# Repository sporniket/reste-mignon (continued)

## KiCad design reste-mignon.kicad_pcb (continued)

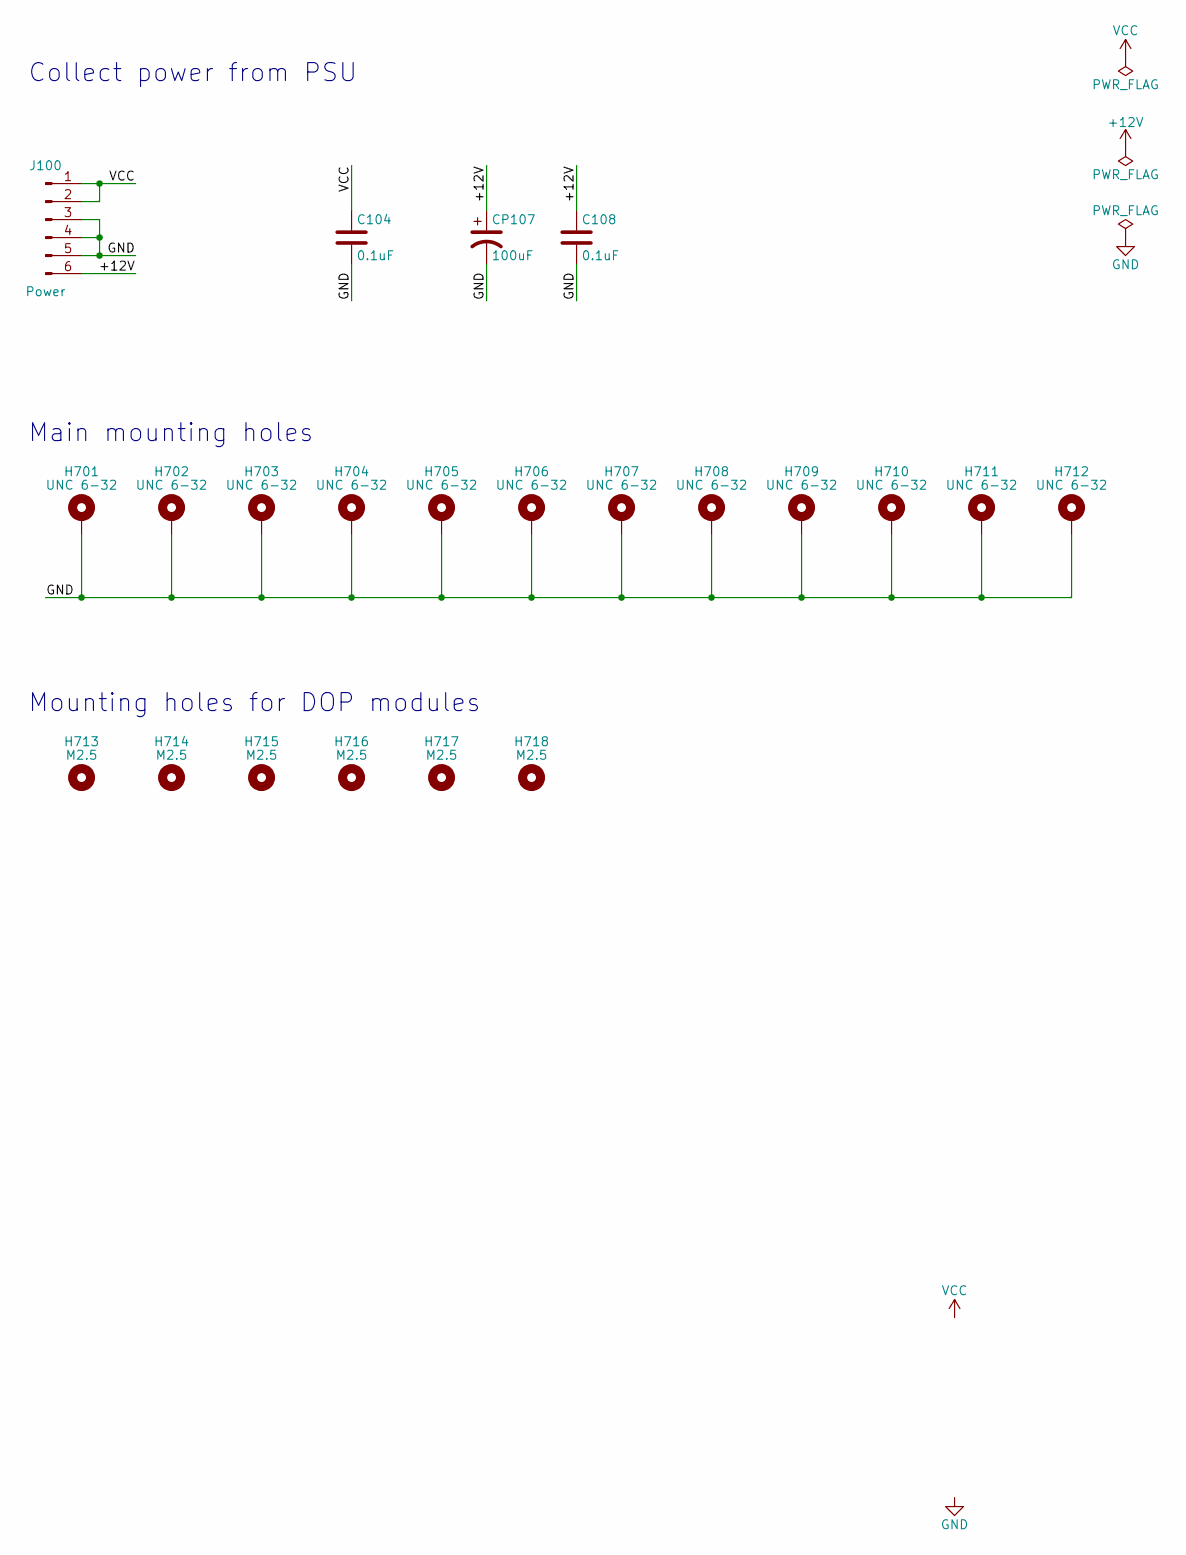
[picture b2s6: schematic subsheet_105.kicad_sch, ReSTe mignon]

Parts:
C104, C108: 0.1uF; C_1206_3216Metric_Pad1.33x1.80mm_HandSolder
CP107: 100uF; C_Radial_D8.0mm_H11.5mm_P3.50mm
H701, H702, H703, H704, H705, H706, H707, H708, H709, H710, H711, H712: UNC 6-32; MountingHole_3.7mm_UTS_6_Pad_Via
H713, H714, H715, H716, H717, H718: M2.5; MountingHole_2.7mm_M2.5_clear_10mm
J100: Power; Molex_KK-254_AE-6410-06A_1x06_P2.54mm_Vertical

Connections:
+12V: C108.1, CP107.1, J100.6
GND: C104.2, C108.2, CP107.2, H701.1, H702.1, H703.1, H704.1, H705.1, H706.1, H707.1, H708.1, H709.1, H710.1, H711.1, H712.1, J100.3, J100.4, J100.5; also elsewhere on the board
VCC: C104.1, J100.1, J100.2; also elsewhere on the board

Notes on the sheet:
Collect power from PSU
Mounting holes for DOP modules
Main mounting holes

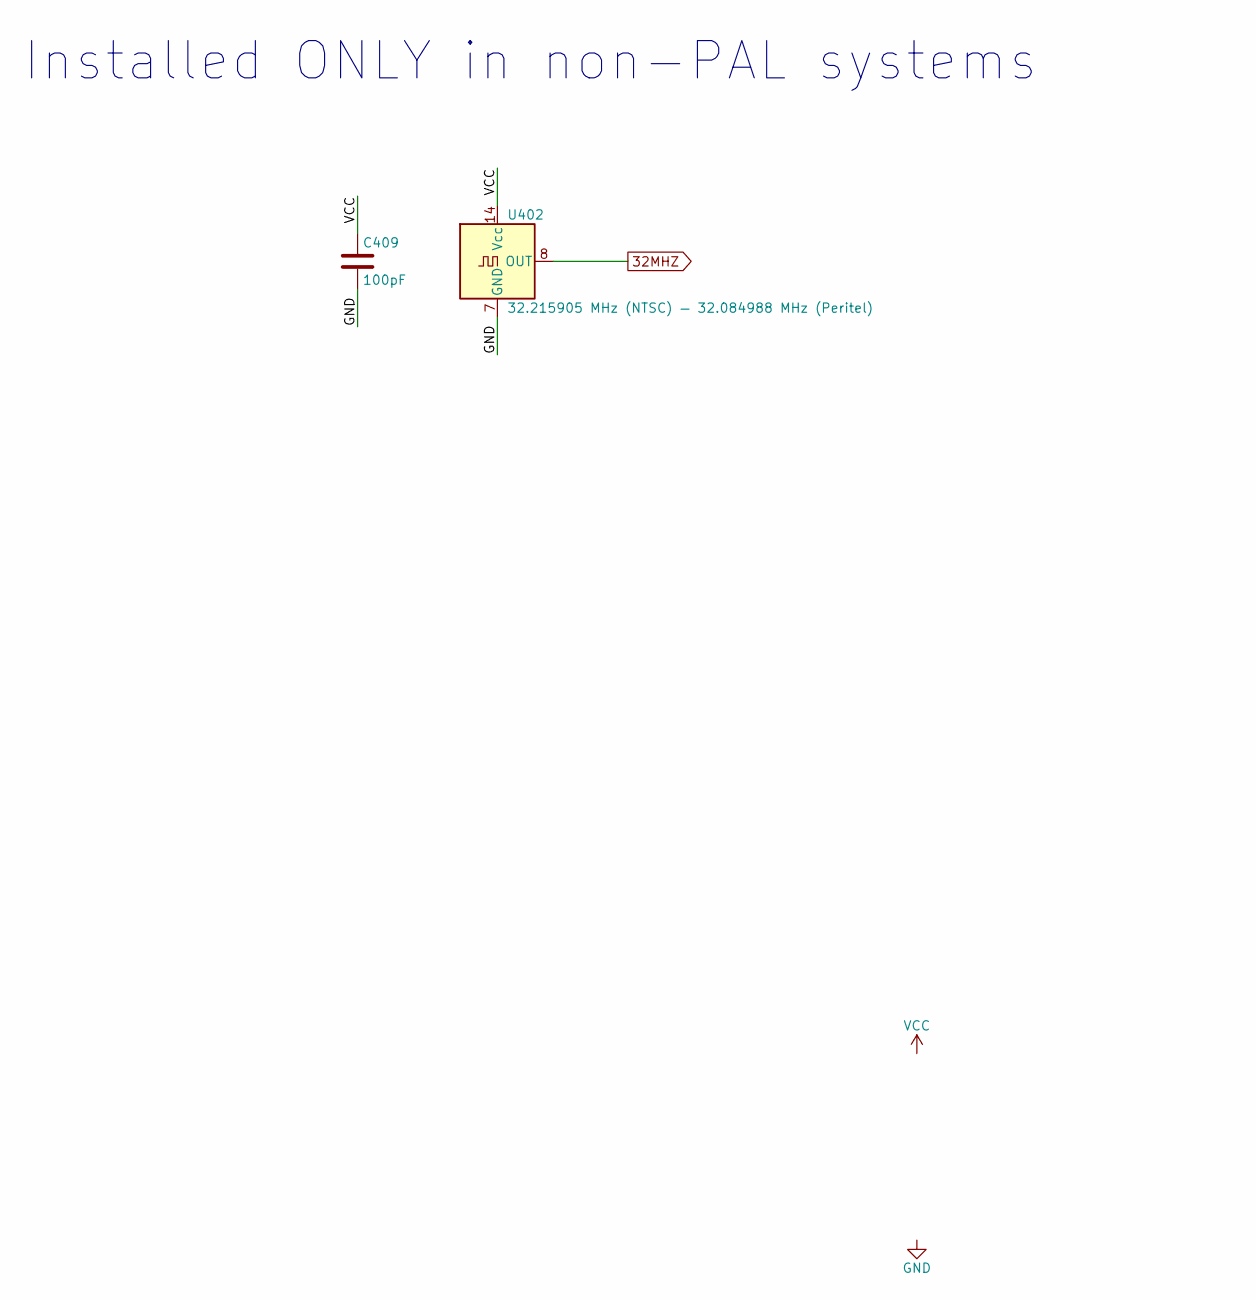
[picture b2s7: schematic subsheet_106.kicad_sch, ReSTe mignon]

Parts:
C409: 100pF; C_1206_3216Metric_Pad1.33x1.80mm_HandSolder
U402: 32.215905 MHz (NTSC) — 32.084988 MHz (Peritel); Oscillator_DIP-14

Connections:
32MHZ: U402.8 (OUT); also elsewhere on the board
GND: C409.2, U402.7 (GND); also elsewhere on the board
VCC: C409.1, U402.14 (Vcc); also elsewhere on the board

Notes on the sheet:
Installed ONLY in non-PAL systems

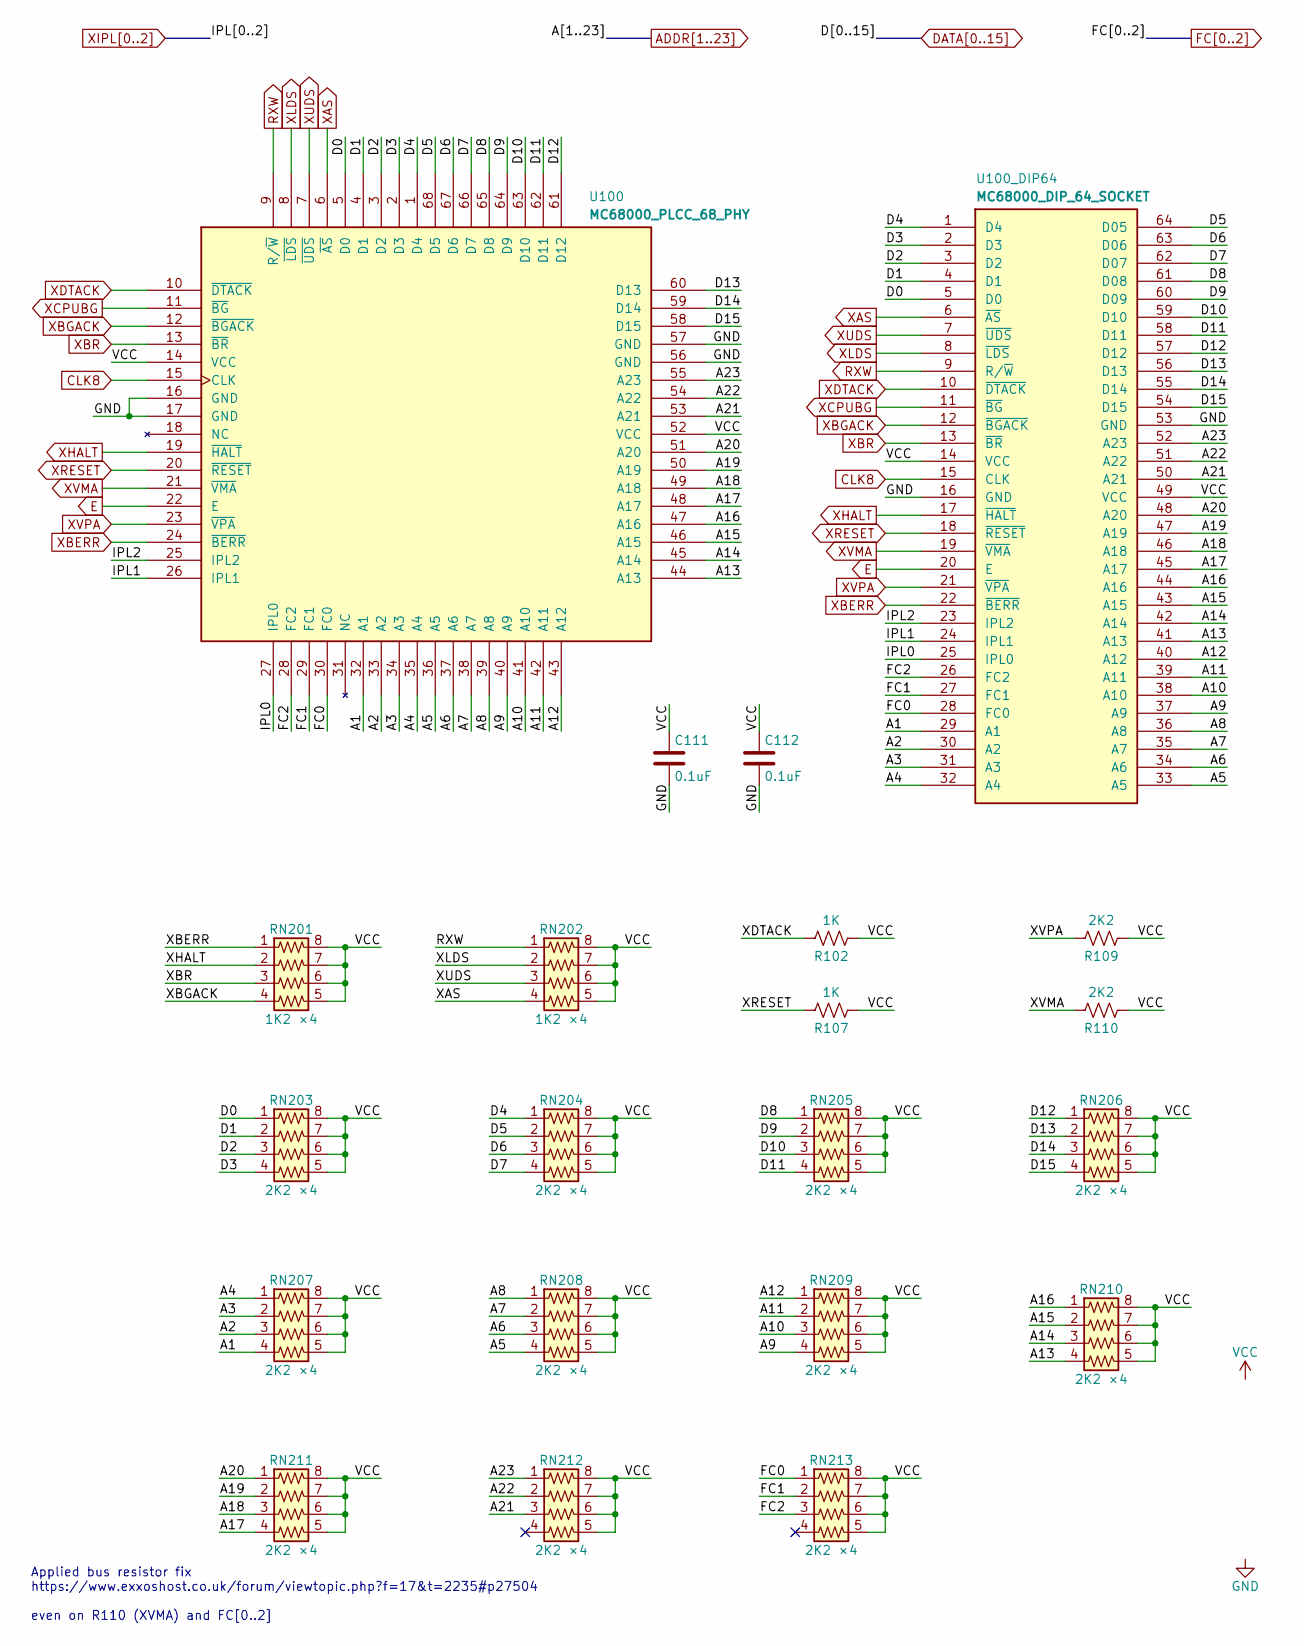
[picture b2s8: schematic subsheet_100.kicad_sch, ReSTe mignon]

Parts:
C111, C112: 0.1uF; C_1206_3216Metric_Pad1.33x1.80mm_HandSolder
R102, R107: 1K; R_1206_3216Metric_Pad1.30x1.75mm_HandSolder
R109, R110: 2K2; R_1206_3216Metric_Pad1.30x1.75mm_HandSolder
RN201, RN202: 1K2 ×4; R_Array_Convex_4x0603
RN203, RN204, RN205, RN206, RN207, RN208, RN209, RN210, RN211, RN212, RN213: 2K2 ×4; R_Array_Convex_4x0603
U100: MC68000_PLCC_68_PHY; PLCC-68_THT-Socket
U100_DIP64: MC68000_DIP_64_SOCKET; DIP-64_W22.86mm_Socket_LongPads

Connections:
ADDR1: RN207.4 (R4.1), U100.32 (A1), U100_DIP64.29 (A1); also elsewhere on the board
ADDR2: RN207.3 (R3.1), U100.33 (A2), U100_DIP64.30 (A2); also elsewhere on the board
ADDR3: RN207.2 (R2.1), U100.34 (A3), U100_DIP64.31 (A3); also elsewhere on the board
ADDR4: RN207.1 (R1.1), U100.35 (A4), U100_DIP64.32 (A4); also elsewhere on the board
ADDR5: RN208.4 (R4.1), U100.36 (A5), U100_DIP64.33 (A5); also elsewhere on the board
ADDR6: RN208.3 (R3.1), U100.37 (A6), U100_DIP64.34 (A6); also elsewhere on the board
ADDR7: RN208.2 (R2.1), U100.38 (A7), U100_DIP64.35 (A7); also elsewhere on the board
ADDR8: RN208.1 (R1.1), U100.39 (A8), U100_DIP64.36 (A8); also elsewhere on the board
ADDR9: RN209.4 (R4.1), U100.40 (A9), U100_DIP64.37 (A9); also elsewhere on the board
ADDR10: RN209.3 (R3.1), U100.41 (A10), U100_DIP64.38 (A10); also elsewhere on the board
ADDR11: RN209.2 (R2.1), U100.42 (A11), U100_DIP64.39 (A11); also elsewhere on the board
ADDR12: RN209.1 (R1.1), U100.43 (A12), U100_DIP64.40 (A12); also elsewhere on the board
ADDR13: RN210.4 (R4.1), U100.44 (A13), U100_DIP64.41 (A13); also elsewhere on the board
ADDR14: RN210.3 (R3.1), U100.45 (A14), U100_DIP64.42 (A14); also elsewhere on the board
ADDR15: RN210.2 (R2.1), U100.46 (A15), U100_DIP64.43 (A15); also elsewhere on the board
ADDR16: RN210.1 (R1.1), U100.47 (A16), U100_DIP64.44 (A16); also elsewhere on the board
ADDR17: RN211.4 (R4.1), U100.48 (A17), U100_DIP64.45 (A17); also elsewhere on the board
ADDR18: RN211.3 (R3.1), U100.49 (A18), U100_DIP64.46 (A18); also elsewhere on the board
ADDR19: RN211.2 (R2.1), U100.50 (A19), U100_DIP64.47 (A19); also elsewhere on the board
ADDR20: RN211.1 (R1.1), U100.51 (A20), U100_DIP64.48 (A20); also elsewhere on the board
ADDR21: RN212.3 (R3.1), U100.53 (A21), U100_DIP64.50 (A21); also elsewhere on the board
ADDR22: RN212.2 (R2.1), U100.54 (A22), U100_DIP64.51 (A22); also elsewhere on the board
ADDR23: RN212.1 (R1.1), U100.55 (A23), U100_DIP64.52 (A23); also elsewhere on the board
CLK8: U100.15 (CLK), U100_DIP64.15 (CLK); also elsewhere on the board
DATA0: RN203.1 (R1.1), U100.5 (D0), U100_DIP64.5 (D0); also elsewhere on the board
DATA1: RN203.2 (R2.1), U100.4 (D1), U100_DIP64.4 (D1); also elsewhere on the board
DATA2: RN203.3 (R3.1), U100.3 (D2), U100_DIP64.3 (D2); also elsewhere on the board
DATA3: RN203.4 (R4.1), U100.2 (D3), U100_DIP64.2 (D3); also elsewhere on the board
DATA4: RN204.1 (R1.1), U100.1 (D4), U100_DIP64.1 (D4); also elsewhere on the board
DATA5: RN204.2 (R2.1), U100.68 (D5), U100_DIP64.64 (D05); also elsewhere on the board
DATA6: RN204.3 (R3.1), U100.67 (D6), U100_DIP64.63 (D06); also elsewhere on the board
DATA7: RN204.4 (R4.1), U100.66 (D7), U100_DIP64.62 (D07); also elsewhere on the board
DATA8: RN205.1 (R1.1), U100.65 (D8), U100_DIP64.61 (D08); also elsewhere on the board
DATA9: RN205.2 (R2.1), U100.64 (D9), U100_DIP64.60 (D09); also elsewhere on the board
DATA10: RN205.3 (R3.1), U100.63 (D10), U100_DIP64.59 (D10); also elsewhere on the board
DATA11: RN205.4 (R4.1), U100.62 (D11), U100_DIP64.58 (D11); also elsewhere on the board
DATA12: RN206.1 (R1.1), U100.61 (D12), U100_DIP64.57 (D12); also elsewhere on the board
DATA13: RN206.2 (R2.1), U100.60 (D13), U100_DIP64.56 (D13); also elsewhere on the board
DATA14: RN206.3 (R3.1), U100.59 (D14), U100_DIP64.55 (D14); also elsewhere on the board
DATA15: RN206.4 (R4.1), U100.58 (D15), U100_DIP64.54 (D15); also elsewhere on the board
E: U100.22 (E), U100_DIP64.20 (E); also elsewhere on the board
FC0: RN213.1 (R1.1), U100.30 (FC0), U100_DIP64.28 (FC0); also elsewhere on the board
FC1: RN213.2 (R2.1), U100.29 (FC1), U100_DIP64.27 (FC1); also elsewhere on the board
FC2: RN213.3 (R3.1), U100.28 (FC2), U100_DIP64.26 (FC2); also elsewhere on the board
GND: C111.2, C112.2, U100.16 (GND), U100.17 (GND), U100.56 (GND), U100.57 (GND), U100_DIP64.16 (GND), U100_DIP64.53 (GND); also elsewhere on the board
RXW: RN202.1 (R1.1), U100.9 (R/~W), U100_DIP64.9 (R/~W); also elsewhere on the board
VCC: C111.1, C112.1, R102.1, R107.1, R109.1, R110.1, RN201.5 (R4.2), RN201.6 (R3.2), RN201.7 (R2.2), RN201.8 (R1.2), RN202.5 (R4.2), RN202.6 (R3.2), RN202.7 (R2.2), RN202.8 (R1.2), RN203.5 (R4.2), RN203.6 (R3.2), RN203.7 (R2.2), RN203.8 (R1.2), RN204.5 (R4.2), RN204.6 (R3.2), RN204.7 (R2.2), RN204.8 (R1.2), RN205.5 (R4.2), RN205.6 (R3.2), RN205.7 (R2.2), RN205.8 (R1.2), RN206.5 (R4.2), RN206.6 (R3.2), RN206.7 (R2.2), RN206.8 (R1.2), RN207.5 (R4.2), RN207.6 (R3.2), RN207.7 (R2.2), RN207.8 (R1.2), RN208.5 (R4.2), RN208.6 (R3.2), RN208.7 (R2.2), RN208.8 (R1.2), RN209.5 (R4.2), RN209.6 (R3.2), RN209.7 (R2.2), RN209.8 (R1.2), RN210.5 (R4.2), RN210.6 (R3.2), RN210.7 (R2.2), RN210.8 (R1.2), RN211.5 (R4.2), RN211.6 (R3.2), RN211.7 (R2.2), RN211.8 (R1.2), RN212.5 (R4.2), RN212.6 (R3.2), RN212.7 (R2.2), RN212.8 (R1.2), RN213.5 (R4.2), RN213.6 (R3.2), RN213.7 (R2.2), RN213.8 (R1.2), U100.14 (VCC), U100.52 (VCC), U100_DIP64.14 (VCC), U100_DIP64.49 (VCC); also elsewhere on the board
XAS: RN202.4 (R4.1), U100.6 (~AS), U100_DIP64.6 (~AS); also elsewhere on the board
XBERR: RN201.1 (R1.1), U100.24 (~BERR), U100_DIP64.22 (~BERR); also elsewhere on the board
XBGACK: RN201.4 (R4.1), U100.12 (~BGACK), U100_DIP64.12 (~BGACK); also elsewhere on the board
XBR: RN201.3 (R3.1), U100.13 (~BR), U100_DIP64.13 (~BR); also elsewhere on the board
XCPUBG: U100.11 (~BG), U100_DIP64.11 (~BG); also elsewhere on the board
XDTACK: R102.2, U100.10 (~DTACK), U100_DIP64.10 (~DTACK); also elsewhere on the board
XHALT: RN201.2 (R2.1), U100.19 (~HALT), U100_DIP64.17 (~HALT); also elsewhere on the board
XIPL0: U100.27 (IPL0), U100_DIP64.25 (IPL0); also elsewhere on the board
XIPL1: U100.26 (IPL1), U100_DIP64.24 (IPL1); also elsewhere on the board
XIPL2: U100.25 (IPL2), U100_DIP64.23 (IPL2); also elsewhere on the board
XLDS: RN202.2 (R2.1), U100.8 (~LDS), U100_DIP64.8 (~LDS); also elsewhere on the board
XRESET: R107.2, U100.20 (~RESET), U100_DIP64.18 (~RESET); also elsewhere on the board
XUDS: RN202.3 (R3.1), U100.7 (~UDS), U100_DIP64.7 (~UDS); also elsewhere on the board
XVMA: R110.2, U100.21 (~VMA), U100_DIP64.19 (~VMA); also elsewhere on the board
XVPA: R109.2, U100.23 (~VPA), U100_DIP64.21 (~VPA); also elsewhere on the board

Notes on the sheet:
Applied bus resistor fix https://www.exxoshost.co.uk/forum/viewtopic.php?f=17&t=2235#p27504 even on R110 (XVMA) and FC[0..2]

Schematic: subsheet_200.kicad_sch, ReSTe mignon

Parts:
C200, C201, C227: 0.1uF; C_1206_3216Metric_Pad1.33x1.80mm_HandSolder
D202: 1N914; D_SOD-123F
J200: DIN-5S — MIDI OUT/THRU; socket-din-5
J201: DIN-5S — MIDI IN; socket-din-5
R207: 220; R_1206_3216Metric_Pad1.30x1.75mm_HandSolder
R209: 1K; R_1206_3216Metric_Pad1.30x1.75mm_HandSolder
RN901: 4K7 ×4; R_Array_Convex_4x0603
RN902: 220 ×4; R_Array_Convex_4x0603
U200: MC6850_PHY; DIP-24_W15.24mm_LongPads
U208: PC900_PHY; DIP-6_W7.62mm_LongPads
U210: 7406_PHY; DIP-14_W7.62mm_LongPads

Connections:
/U200 — Acia 1 to MIDI IO/midi_out: RN902.4 (R4.1), U210.8 (4Y)
/U200 — Acia 1 to MIDI IO/midi_thru: RN902.3 (R3.1), U210.10 (5Y)
/U200 — Acia 1 to MIDI IO/not_rx: RN901.2 (R2.1), U210.11 (5A), U210.12 (6Y)
/U200 — Acia 1 to MIDI IO/not_tx: RN901.3 (R3.1), U210.6 (3Y), U210.9 (4A)
/U200 — Acia 1 to MIDI IO/rx: RN901.1 (R1.1), U200.2 (RXDAT), U208.4 (VO), U210.13 (6A)
/U200 — Acia 1 to MIDI IO/tx: U200.6 (TXDAT), U210.5 (3A)
ACIA_IRQ: R209.1, U200.7 (~IRQ); also elsewhere on the board
ADDR1: U200.11 (RS); also elsewhere on the board
ADDR2: U200.10 (CS1); also elsewhere on the board
DATA8: U200.22 (D0); also elsewhere on the board
DATA9: U200.21 (D1); also elsewhere on the board
DATA10: U200.20 (D2); also elsewhere on the board
DATA11: U200.19 (D3); also elsewhere on the board
DATA12: U200.18 (D4); also elsewhere on the board
DATA13: U200.17 (D5); also elsewhere on the board
DATA14: U200.16 (D6); also elsewhere on the board
DATA15: U200.15 (D7); also elsewhere on the board
E: U200.14 (E); also elsewhere on the board
GND: C200.2, C201.2, C227.2, J200.2, J200.SH (Shield), J201.SH (Shield), U200.1 (GND), U200.9 (~CS2), U200.23 (~DCD), U200.24 (~CTS), U208.5 (GND), U210.7 (GND); also elsewhere on the board
KHZ500: U200.3 (TXCLK), U200.4 (RXCLK); also elsewhere on the board
N6850: U200.8 (CS0); also elsewhere on the board
unnamed: D202.2 (A), J201.5, U208.2 (Cathode)
unnamed: D202.1 (K), R207.2, U208.1 (Anode)
unnamed: J200.1, RN902.8 (R1.2)
unnamed: J200.3, RN902.6 (R3.2)
unnamed: J200.4, RN902.7 (R2.2)
unnamed: J200.5, RN902.5 (R4.2)
unnamed: J201.4, R207.1
RESET: U210.1 (1A), U210.3 (2A); also elsewhere on the board
RXW: U200.13 (R/~W); also elsewhere on the board
VCC: C200.1, C201.1, C227.1, R209.2, RN901.5 (R4.2), RN901.6 (R3.2), RN901.7 (R2.2), RN901.8 (R1.2), RN902.1 (R1.1), RN902.2 (R2.1), U200.12 (Vcc), U208.6 (Vcc), U210.14 (Vcc); also elsewhere on the board
XHALT: U210.4 (2Y); also elsewhere on the board
XRESET: U210.2 (1Y); also elsewhere on the board

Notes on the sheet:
WARNING ! The pinout is mirrored.

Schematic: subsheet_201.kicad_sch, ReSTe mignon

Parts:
C210, C1001: 0.1uF; C_1206_3216Metric_Pad1.33x1.80mm_HandSolder
C1002, C1003: 1nF; C_1206_3216Metric_Pad1.33x1.80mm_HandSolder
J202: BRS — To IKBD; PinHeader_1x08_P2.54mm_Vertical_Ikbd
J1001: RJ11S - To Mega ST(e)/TT Keyboard; RJ12_Amphenol_54601
R210: 10K; R_1206_3216Metric_Pad1.30x1.75mm_HandSolder
U201: MC6850_PHY; DIP-24_W15.24mm_LongPads

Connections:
/U201 — Acia 2 to IKBD IO/rx: C1003.1, J202.5, J1001.4, R210.1, U201.2 (RXDAT)
/U201 — Acia 2 to IKBD IO/tx: C1002.1, J202.6, J1001.3, U201.6 (TXDAT)
ACIA_IRQ: U201.7 (~IRQ); also elsewhere on the board
ADDR1: U201.11 (RS); also elsewhere on the board
ADDR2: U201.9 (~CS2); also elsewhere on the board
BD0SEL: J202.3; also elsewhere on the board
DATA8: U201.22 (D0); also elsewhere on the board
DATA9: U201.21 (D1); also elsewhere on the board
DATA10: U201.20 (D2); also elsewhere on the board
DATA11: U201.19 (D3); also elsewhere on the board
DATA12: U201.18 (D4); also elsewhere on the board
DATA13: U201.17 (D5); also elsewhere on the board
DATA14: U201.16 (D6); also elsewhere on the board
DATA15: U201.15 (D7); also elsewhere on the board
E: U201.14 (E); also elsewhere on the board
GND: C210.2, C1001.2, C1002.2, C1003.2, J202.1, J202.8, J1001.5, J1001.6, U201.1 (GND), U201.23 (~DCD), U201.24 (~CTS); also elsewhere on the board
KHZ500: U201.3 (TXCLK), U201.4 (RXCLK); also elsewhere on the board
N6850: U201.8 (CS0); also elsewhere on the board
RXW: U201.13 (R/~W); also elsewhere on the board
VCC: C210.1, C1001.1, J202.4, J1001.1, J1001.2, R210.2, U201.10 (CS1), U201.12 (Vcc); also elsewhere on the board
XRESET: J202.7; also elsewhere on the board

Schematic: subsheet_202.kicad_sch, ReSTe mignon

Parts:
C214: 0.1uF; C_1206_3216Metric_Pad1.33x1.80mm_HandSolder
J203: DB-25S Parallel port; DSUB-25_Female_Horizontal_P2.77x2.84mm_EdgePinOffset7.70mm_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
J1101: Parallel and Serial breakout; PinHeader_2x14_P2.54mm_Vertical
R212: 3K3; R_1206_3216Metric_Pad1.30x1.75mm_HandSolder
R220: 1K; R_1206_3216Metric_Pad1.30x1.75mm_HandSolder
U202: YM2149_PHY; DIP-40_W15.24mm_LongPads

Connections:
/U202 — PSG and Parallel IO/pd0: J203.2, J1101.5, U202.13 (IOB0)
/U202 — PSG and Parallel IO/pd1: J203.3, J1101.7, U202.12 (IOB1)
/U202 — PSG and Parallel IO/pd2: J203.4, J1101.9, U202.11 (IOB2)
/U202 — PSG and Parallel IO/pd3: J203.5, J1101.11, U202.10 (IOB3)
/U202 — PSG and Parallel IO/pd4: J203.6, J1101.13, U202.9 (IOB4)
/U202 — PSG and Parallel IO/pd5: J203.7, J1101.15, U202.8 (IOB5)
/U202 — PSG and Parallel IO/pd6: J203.8, J1101.17, U202.7 (IOB6)
/U202 — PSG and Parallel IO/pd7: J203.9, J1101.19, U202.6 (IOB7)
/U202 — PSG and Parallel IO/strobe: J203.1, J1101.3, U202.16 (IOA5)
AUDIOS: R220.2, U202.3 (ACA), U202.4 (ACB), U202.38 (ACC); also elsewhere on the board
CLK2: U202.22 (CLOCK); also elsewhere on the board
D0SEL: U202.20 (IOA1); also elsewhere on the board
D1SEL: U202.19 (IOA2); also elsewhere on the board
DATA8: U202.37 (DA0); also elsewhere on the board
DATA9: U202.36 (DA1); also elsewhere on the board
DATA10: U202.35 (DA2); also elsewhere on the board
DATA11: U202.34 (DA3); also elsewhere on the board
DATA12: U202.33 (DA4); also elsewhere on the board
DATA13: U202.32 (DA5); also elsewhere on the board
DATA14: U202.31 (DA6); also elsewhere on the board
DATA15: U202.30 (DA7); also elsewhere on the board
GND: C214.2, J203.18, J203.19, J203.20, J203.21, J203.22, J203.23, J203.24, J203.25, J203.SH (Shield), J1101.2, J1101.4, J1101.6, J1101.8, J1101.10, J1101.12, J1101.14, J1101.16, J1101.18, J1101.20, J1101.22, J1101.24, J1101.26, J1101.28, R220.1, U202.1 (GND), U202.24 (~A9); also elsewhere on the board
PARALLEL_BUSY: J203.11, J1101.1, R212.2; also elsewhere on the board
S0SEL: U202.21 (IOA0); also elsewhere on the board
SERIAL_DIR: U202.17 (IOA4); also elsewhere on the board
SERIAL_RTS: U202.18 (IOA3); also elsewhere on the board
SERIAL_RX: J1101.25; also elsewhere on the board
SERIAL_TX: J1101.27; also elsewhere on the board
SNDCS: U202.29 (BC1); also elsewhere on the board
SNDIR: U202.27 (BDIR); also elsewhere on the board
VCC: C214.1, J1101.21, J1101.23, R212.1, U202.25 (A8), U202.28 (BC2), U202.40 (Vcc); also elsewhere on the board
XRESET: U202.23 (~RESET); also elsewhere on the board

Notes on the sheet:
To LMC1992
To MFP

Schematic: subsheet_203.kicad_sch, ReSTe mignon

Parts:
C219, C220: 30pF; C_1206_3216Metric_Pad1.33x1.80mm_HandSolder
C221, C229, C230, C900: 0.1uF; C_1206_3216Metric_Pad1.33x1.80mm_HandSolder
R215, R216, R217: 4K7; R_1206_3216Metric_Pad1.30x1.75mm_HandSolder
U203: MC68901_DIP_48_PHY; DIP-48_W15.24mm_Socket_LongPads
U209: 74LS86_PHY; DIP-14_W7.62mm_LongPads
U211: 74LS04_PHY; DIP-14_W7.62mm_LongPads
U900: 74LS164_PHY; DIP-14_W7.62mm_LongPads
Y200: 2.4576 MHz; Crystal_HC18-U_Horizontal

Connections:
/U203 — MFP 68901/hsync_xor_vsync: U209.3 (1Y), U211.5 (3A)
/U203 — MFP 68901/not_xsint: U209.13 (4B), U211.2 (1Y), U900.1 (A), U900.2 (B), U900.9 (~CLR)
/U203 — MFP 68901/not_xsint_XOR_monomon: U203.29 (I7), U209.11 (4Y)
/U203 — MFP 68901/tai: U203.19 (TAI), U900.13 (QH)
/U203 — MFP 68901/timer_d: U203.7 (TC), U203.10 (RC), U203.16 (TDO)
/U203 — MFP 68901/xtal1: C220.1, U203.17 (XTAL1), Y200.2
/U203 — MFP 68901/xtal2: C219.1, U203.18 (XTAL2), Y200.1
ACIA_IRQ: U203.26 (I4); also elsewhere on the board
ADDR1: U203.2 (RS1); also elsewhere on the board
ADDR2: U203.3 (RS2); also elsewhere on the board
ADDR3: U203.4 (RS3); also elsewhere on the board
ADDR4: U203.5 (RS4); also elsewhere on the board
ADDR5: U203.6 (RS5); also elsewhere on the board
CLK2: U900.8 (CLK); also elsewhere on the board
CLK4: U203.35 (CLK); also elsewhere on the board
DATA0: U203.37 (D0); also elsewhere on the board
DATA1: U203.38 (D1); also elsewhere on the board
DATA2: U203.39 (D2); also elsewhere on the board
DATA3: U203.40 (D3); also elsewhere on the board
DATA4: U203.41 (D4); also elsewhere on the board
DATA5: U203.42 (D5); also elsewhere on the board
DATA6: U203.43 (D6); also elsewhere on the board
DATA7: U203.44 (D7); also elsewhere on the board
DE: U203.20 (TBI); also elsewhere on the board
GND: C219.2, C220.2, C221.2, C229.2, C230.2, C900.2, U203.34 (~IEI), U203.36 (GND), U209.4 (2A), U209.5 (2B), U209.7 (GND), U209.9 (3A), U209.10 (3B), U211.7 (GND), U211.9 (4A), U211.11 (5A), U211.13 (6A), U900.7 (GND); also elsewhere on the board
HSYNC: U209.1 (1A); also elsewhere on the board
MONOMON: R215.1, U209.12 (4A); also elsewhere on the board
PARALLEL_BUSY: U203.22 (I0); also elsewhere on the board
RXW: U203.1 (R/~W); also elsewhere on the board
SD7: U211.4 (2Y); also elsewhere on the board
SERIAL_CD: U203.23 (I1); also elsewhere on the board
SERIAL_CTS: U203.24 (I2); also elsewhere on the board
SERIAL_RI: U203.28 (I6); also elsewhere on the board
SERIAL_RX: U203.9 (SI); also elsewhere on the board
SERIAL_TX: U203.8 (SO); also elsewhere on the board
SHIFTER_SD7: U211.3 (2A); also elsewhere on the board
VCC: C221.1, C229.1, C230.1, C900.1, R215.2, R216.2, R217.2, U203.11 (VCC), U209.14 (Vcc), U211.14 (Vcc), U900.14 (Vcc); also elsewhere on the board
VSYNC: U209.2 (1B); also elsewhere on the board
XBLTINT: R216.1, U203.25 (I3); also elsewhere on the board
XDISKINT: U203.27 (I5); also elsewhere on the board
XDTACK: U203.46 (~DTACK); also elsewhere on the board
XIACK: U203.45 (~IACK); also elsewhere on the board
XLDS: U203.47 (~DS); also elsewhere on the board
XMFPCS: U203.48 (~CS); also elsewhere on the board
XMFPINT: R217.1, U203.32 (~IRQ); also elsewhere on the board
XRESET: U203.21 (~RESET); also elsewhere on the board
XSINT: U211.1 (1A); also elsewhere on the board

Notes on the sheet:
TODO : verify that HSYNC xor VSYNC is no more used

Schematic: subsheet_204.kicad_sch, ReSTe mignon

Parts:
C203, C206, C228: 0.1uF; C_1206_3216Metric_Pad1.33x1.80mm_HandSolder
C222, C223, C224, C225: 100pF; C_1206_3216Metric_Pad1.33x1.80mm_HandSolder
J204: DB-25P Serial Port RS-232; DSUB-25_Male_Horizontal_P2.77x2.84mm_EdgePinOffset7.70mm_Ho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
U206: MC1488_QUAD_LINE_EIA-232D_DRIVER_PHY; DIP-14_W7.62mm_LongPads
U207: MC1489_QUAD_LINE_EIA-232D_RECEIVERS_PHY; DIP-14_W7.62mm_LongPads

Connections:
-12V: C203.1, U206.1 (VEE); also elsewhere on the board
/J204 — RS-232 IO/rca: C222.1, U207.2 (RCA)
/J204 — RS-232 IO/rcb: C223.1, U207.5 (RCB)
/J204 — RS-232 IO/rcc: C225.1, U207.9 (RCC)
/J204 — RS-232 IO/rcd: C224.1, U207.12 (RCD)
/J204 — RS-232 IO/rs_232_cd: J204.8, U207.13 (ID)
/J204 — RS-232 IO/rs_232_cts: J204.5, U207.4 (IB)
/J204 — RS-232 IO/rs_232_dir: J204.20, U206.3 (OA)
/J204 — RS-232 IO/rs_232_ri: J204.22, U207.10 (IC)
/J204 — RS-232 IO/rs_232_rts: J204.4, U206.8 (OC)
/J204 — RS-232 IO/rs_232_rx: J204.3, U207.1 (IA)
/J204 — RS-232 IO/rs_232_tx: J204.2, U206.6 (OB)
G12V: C206.1, U206.14 (Vcc); also elsewhere on the board
GND: C203.2, C206.2, C222.2, C223.2, C224.2, C225.2, C228.2, J204.1, J204.7, J204.SH (Shield), U206.7 (GND), U206.12 (ID2), U206.13 (ID1), U207.7 (GND); also elsewhere on the board
SERIAL_CD: U207.11 (OD); also elsewhere on the board
SERIAL_CTS: U207.6 (OB); also elsewhere on the board
SERIAL_DIR: U206.2 (IA); also elsewhere on the board
SERIAL_RI: U207.8 (OC); also elsewhere on the board
SERIAL_RTS: U206.9 (IC2), U206.10 (IC1); also elsewhere on the board
SERIAL_RX: U207.3 (OA); also elsewhere on the board
SERIAL_TX: U206.4 (IB1), U206.5 (IB2); also elsewhere on the board
VCC: C228.1, U207.14 (Vcc); also elsewhere on the board

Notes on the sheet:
TODO : replace by a DB-9P Serial Port

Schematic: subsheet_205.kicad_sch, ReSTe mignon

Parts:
C207, C217: 0.1uF; C_1206_3216Metric_Pad1.33x1.80mm_HandSolder
C208: 150pF; C_1206_3216Metric_Pad1.33x1.80mm_HandSolder
C209: 330pF; C_1206_3216Metric_Pad1.33x1.80mm_HandSolder
C218: 270pF; C_1206_3216Metric_Pad1.33x1.80mm_HandSolder
CP202, CP204, CP205, CP215: 4.7uF; C_Radial_D5.0mm_H11.0mm_P2.00mm
CP216: 470uF; C_Radial_D12.5mm_H20.0mm_P5.00mm
D200, D201, D203: 1N914; D_SOD-123F
L203, L208: 220uH; L_Radial_D15.0mm_P5.00mm
R203: 5.1; R_1206_3216Metric_Pad1.30x1.75mm_HandSolder
R206: 12K; R_1206_3216Metric_Pad1.30x1.75mm_HandSolder
R208, R213: 1K2; R_1206_3216Metric_Pad1.30x1.75mm_HandSolder
R211: 1; R_1206_3216Metric_Pad1.30x1.75mm_HandSolder
R214: 3K9; R_1206_3216Metric_Pad1.30x1.75mm_HandSolder
U204, U205: TL497A_DIP-14_500MA_PEAK_STEP-UP_STEP-DOWN_INVERT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; DIP-14_W7.62mm_LongPads

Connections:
-5V: CP215.2, CP216.2, D203.2 (A), R213.1, U205.4 (SUBSTRATE); also elsewhere on the board
-12V: CP204.2, D200.2 (A); also elsewhere on the board
/U204 U205 — G12V -12V -5V/col_1: CP202.1, L203.2, U204.7 (ANODE), U204.10 (COL_OUT)
/U204 U205 — G12V -12V -5V/freq_1: C209.1, U204.3 (FREQ_CONTROL)
/U204 U205 — G12V -12V -5V/freq_2: C218.1, U205.3 (FREQ_CONTROL)
/U204 U205 — G12V -12V -5V/in_1: R206.2, R208.1, U204.1 (COMP_INPUT)
/U204 U205 — G12V -12V -5V/in_2: R213.2, R214.1, U205.1 (COMP_INPUT)
/U204 U205 — G12V -12V -5V/lim_1: C208.1, L203.1, R203.1, U204.13 (CUR_LIM_SENSE)
G12V: CP205.1, R206.1, U204.6 (CATHODE); also elsewhere on the board
GND: C207.2, C208.2, C209.2, C217.2, C218.2, CP204.1, CP205.2, CP215.1, CP216.1, D201.1 (K), L208.2, R208.2, R214.2, U204.2 (INHIBIT), U204.4 (SUBSTRATE), U204.5 (GND), U204.8 (EMIT_OUT), U205.2 (INHIBIT), U205.5 (GND); also elsewhere on the board
unnamed: CP202.2, D200.1 (K), D201.2 (A)
unnamed: D203.1 (K), L208.1, U205.8 (EMIT_OUT)
unnamed: R211.2, U205.10 (COL_OUT), U205.13 (CUR_LIM_SENSE)
VCC: C207.1, C217.1, R203.2, R211.1, U204.14 (Vcc), U205.14 (Vcc); also elsewhere on the board

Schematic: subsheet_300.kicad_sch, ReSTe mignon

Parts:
C226, C302: 0.1uF; C_1206_3216Metric_Pad1.33x1.80mm_HandSolder
R303: 1K; R_1206_3216Metric_Pad1.30x1.75mm_HandSolder
RN1501, RN1502: 10K ×4; R_Array_Convex_4x0603
U300_DIP40: ST_DMA_DIP40_PHY; DIP-40_W15.24mm_Socket_LongPads
U300_PLCC44: ST_DMA_PLCC44_PHY; PLCC-44_THT-Socket

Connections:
ADDR1: U300_DIP40.2 (A1), U300_PLCC44.2 (A1); also elsewhere on the board
CADDR1: U300_DIP40.26 (CA1), U300_PLCC44.28 (CA1); also elsewhere on the board
CADDR2: U300_DIP40.27 (CA2), U300_PLCC44.29 (CA2); also elsewhere on the board
CDATA0: RN1501.1 (R1.1), U300_DIP40.36 (CD0), U300_PLCC44.39 (CD0); also elsewhere on the board
CDATA1: RN1501.2 (R2.1), U300_DIP40.35 (CD1), U300_PLCC44.38 (CD1); also elsewhere on the board
CDATA2: RN1501.3 (R3.1), U300_DIP40.34 (CD2), U300_PLCC44.37 (CD2); also elsewhere on the board
CDATA3: RN1501.4 (R4.1), U300_DIP40.33 (CD3), U300_PLCC44.36 (CD3); also elsewhere on the board
CDATA4: RN1502.1 (R1.1), U300_DIP40.32 (CD4), U300_PLCC44.35 (CD4); also elsewhere on the board
CDATA5: RN1502.2 (R2.1), U300_DIP40.31 (CD5), U300_PLCC44.34 (CD5); also elsewhere on the board
CDATA6: RN1502.3 (R3.1), U300_DIP40.30 (CD6), U300_PLCC44.33 (CD6); also elsewhere on the board
CDATA7: RN1502.4 (R4.1), U300_DIP40.29 (CD7), U300_PLCC44.31 (CD7); also elsewhere on the board
CLK8: U300_DIP40.39 (CLK), U300_PLCC44.43 (CLK); also elsewhere on the board
DATA0: U300_DIP40.4 (D0), U300_PLCC44.5 (D0); also elsewhere on the board
DATA1: U300_DIP40.5 (D1), U300_PLCC44.6 (D1); also elsewhere on the board
DATA2: U300_DIP40.6 (D2), U300_PLCC44.7 (D2); also elsewhere on the board
DATA3: U300_DIP40.7 (D3), U300_PLCC44.8 (D3); also elsewhere on the board
DATA4: U300_DIP40.8 (D4), U300_PLCC44.9 (D4); also elsewhere on the board
DATA5: U300_DIP40.9 (D5), U300_PLCC44.10 (D5); also elsewhere on the board
DATA6: U300_DIP40.10 (D6), U300_PLCC44.11 (D6); also elsewhere on the board
DATA7: U300_DIP40.11 (D7), U300_PLCC44.12 (D7); also elsewhere on the board
DATA8: U300_DIP40.12 (D8), U300_PLCC44.13 (D8); also elsewhere on the board
DATA9: U300_DIP40.13 (D9), U300_PLCC44.14 (D9); also elsewhere on the board
DATA10: U300_DIP40.14 (D10), U300_PLCC44.15 (D10); also elsewhere on the board
DATA11: U300_DIP40.15 (D11), U300_PLCC44.16 (D11); also elsewhere on the board
DATA12: U300_DIP40.16 (D12), U300_PLCC44.17 (D12); also elsewhere on the board
DATA13: U300_DIP40.17 (D13), U300_PLCC44.18 (D13); also elsewhere on the board
DATA14: U300_DIP40.18 (D14), U300_PLCC44.19 (D14); also elsewhere on the board
DATA15: U300_DIP40.19 (D15), U300_PLCC44.20 (D15); also elsewhere on the board
DMA_ACK: U300_DIP40.37 (~ACK), U300_PLCC44.40 (~ACK); also elsewhere on the board
DMA_FDCS: U300_DIP40.22 (~FDCS), U300_PLCC44.24 (~FDCS); also elsewhere on the board
DMA_FDRQ: U300_DIP40.21 (FDRQ), U300_PLCC44.23 (FDRQ); also elsewhere on the board
DMA_HDCS: U300_DIP40.24 (~HDCS), U300_PLCC44.26 (~HDCS); also elsewhere on the board
DMA_HDRQ: U300_DIP40.23 (HDRQ), U300_PLCC44.25 (HDRQ); also elsewhere on the board
DMA_RW: U300_DIP40.25 (CR/~W), U300_PLCC44.27 (CR/~W); also elsewhere on the board
GND: C226.2, C302.2, U300_DIP40.20 (GND), U300_DIP40.28 (GND), U300_PLCC44.4 (GND), U300_PLCC44.22 (GND), U300_PLCC44.30 (TESTIN), U300_PLCC44.32 (GND), U300_PLCC44.42 (GND); also elsewhere on the board
RDY: R303.1, U300_DIP40.38 (RDY), U300_PLCC44.41 (RDY); also elsewhere on the board
RXW: U300_DIP40.1 (R/~W), U300_PLCC44.1 (R/~W); also elsewhere on the board
VCC: C226.1, C302.1, R303.2, RN1501.5 (R4.2), RN1501.6 (R3.2), RN1501.7 (R2.2), RN1501.8 (R1.2), RN1502.5 (R4.2), RN1502.6 (R3.2), RN1502.7 (R2.2), RN1502.8 (R1.2), U300_DIP40.40 (Vcc), U300_PLCC44.21 (Vcc), U300_PLCC44.44 (Vcc); also elsewhere on the board
XFCS: U300_DIP40.3 (~FCS), U300_PLCC44.3 (~FCS); also elsewhere on the board

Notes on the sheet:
I found out that C226 is not present in sheet 2. Thus I believe that it is in fact the second bypass capacitor for U300.
For motherboards with PLCC-44 version (my motherboard), pinout taken from the schematics of the Mega STE and the STBook
For motherboards with DIP-40 version (original schematics)
DMA data bus pull-up fix https://www.exxoshost.co.uk/forum/viewtopic.php?f=17&t=1417
